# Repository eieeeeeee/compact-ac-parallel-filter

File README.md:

# Compact AC Parallel Filter

Open-hardware research platform for compact plug-in AC-noise filtering and adaptive parallel-shunt control.

> [!WARNING]
> **PRE-PROTOTYPE / EXPERIMENTAL / NOT MAINS-VALIDATED**
>
> No RC18 physical prototype has yet been manufactured or validated on hazardous mains power. The RC18 active-control work in this repository is currently a **low-voltage architecture and simulation study**. A safe mains coupling/isolation implementation is **not defined by the RC18 simulation model**. Do not interpret simulation, KiCad DRC/ERC, or CI results as safety approval, PSE compliance, EMC certification, or production readiness.

## What makes this repository different

The project publishes not only schematics and PCB files, but also the assumptions, comparison baseline, dense frequency sweeps, corner cases, controller coefficients, numerical implementation checks, and machine-executable pass/fail gates used to make design decisions.

A design change should be able to answer a simple question automatically:

> Does this change still meet the frozen electrical gates, or not?

## Current research branches

| Track | Purpose | State |
|---|---|---|
| Passive plug-in network | Compact X2/MOV/fuse parallel network | Pre-prototype |
| Rev.D / RC17 | Frozen comparison baseline for adaptive active-shunt studies | Simulation reference |
| **RC18-B2.1** | Lower-cost EPC23104 + 3 MHz + asymmetric 3-stage reconstruction + digital biquad | **Simulation gate PASS candidate** |

## RC18-B2.1 frozen candidate

The active-control candidate currently under validation is intentionally kept separate from the mains-safety question.

### Power/control architecture

- EPC23104 integrated GaN power stage
- 3.0 MHz PWM
- 2.0 MHz digital control update
- 0.82 µH / 150 nF first reconstruction section
- 0.47 µH / 100 nF second section
- 0.68 µH / 82 nF third section
- final float32/Q31 biquad validation at total modeled latency 2.041 µs
- bounded timing jitter: ±25 ns

### Frozen digital biquad

```text
H(z) = (b0 + b1 z^-1 + b2 z^-2) / (1 + a1 z^-1 + a2 z^-2)

b0 =  1.96005549
b1 = -2.81840199
b2 =  0.92560172
a1 = -1.02969083
a2 =  0.09694605
Fs = 2.000 MHz
```

### Electrical simulation gates

The CI gate evaluates:

- 241 logarithmic points from 5–30 kHz
- 241 logarithmic points from 30–100 kHz for watchdog testing
- source |Z| = 0.2 / 0.5 / 1 / 2 / 5 / 10 / 20 Ω
- source phase = −60° to +60° in 15° steps
- B2.1 nominal, low-L/C and high-L/C corners
- float32 sequential arithmetic
- Q31 CMSIS-style DF1 arithmetic model
- ±25 ns bounded timing jitter
- active current ceiling = 120 mArms
- command ceiling = 3.39411255 Vrms
- watchdog worsening ≤ +0.5 dB
- strict same-model RC17 equivalence requirement

The current self-contained validation script passes both float32 and Q31 gates. The exact result is regenerated in CI rather than accepted from a hand-edited table.

## Reproduce the RC18 gate locally

```bash
python -m pip install -r simulations/rc18-b2.1/requirements.txt
python simulations/rc18-b2.1/validate_rc18.py
```

Generated results are written under `validation/rc18-b2.1/generated/` by default.

See:

- [`docs/RC18-B2.1-VALIDATION-SPEC.md`](docs/RC18-B2.1-VALIDATION-SPEC.md)
- [`docs/REPRODUCIBILITY.md`](docs/REPRODUCIBILITY.md)
- [`simulations/rc18-b2.1/README.md`](simulations/rc18-b2.1/README.md)
- [`firmware/rc18-b2.1/biquad_coeffs.h`](firmware/rc18-b2.1/biquad_coeffs.h)
- [`validation/rc18-b2.1/README.md`](validation/rc18-b2.1/README.md)

## Repository structure

```text
.
├─ .github/workflows/          # KiCad and electrical validation CI
├─ hardware/                   # KiCad design work
├─ firmware/                   # Controller implementation material
├─ simulations/                # Reproducible models and gate scripts
├─ validation/                 # Frozen reference and generated results
├─ measurements/               # Physical measurements when prototypes exist
├─ bom/                        # BOM and sourcing work
├─ docs/                       # Design decisions, test plans, validation specs
├─ SAFETY.md
├─ CONTRIBUTING.md
├─ CITATION.cff
└─ LICENSE
```

## Evidence policy

Simulation results are predictions from disclosed models, not measurements. Null results, failed revisions, regressions, and negative measurements are part of the engineering record and should not be hidden.

Claims about real-world noise reduction will require controlled measurements using the same noise source, wiring, instrument settings, and comparison procedure. A future validated release should include raw data sufficient for independent re-analysis.

## Development path

`pre-prototype → low-voltage bench validation → isolated/safe interface design → controlled prototype test → independent reproduction → validated release`

A `v1.0` tag is reserved for a release whose documentation matches physically tested hardware.

## Safety and regulatory note

Open-source publication does not imply Japanese PSE compliance, IEC/UL compliance, EMC certification, safety approval, or fitness for connection to the public mains network. KiCad ERC/DRC only checks defined CAD rules; it cannot prove electrical safety or regulatory conformity.

Read [`SAFETY.md`](SAFETY.md) before working with any mains-related hardware in this repository.

## License

Hardware source material is published under **CERN-OHL-W-2.0** as described in [`LICENSE`](LICENSE).

---

## 日本語概要

このリポジトリは、コンセント直挿し型の並列ノイズ対策回路と、適応型アクティブ・シャント制御を研究するオープンハードウェア・プロジェクトです。

RC18では「回路図を公開する」だけではなく、比較基準、241点の周波数掃引、部品ばらつき、0.2～20 Ωのライン条件、±60°位相、watchdog、float32/Q31量子化、演算誤差、タイミングジッタまで公開し、GitHub Actionsで自動的にPASS/FAILを判定できる形を目指しています。

RC18-B2.1は現時点で**低電圧アーキテクチャのシミュレーション候補**です。商用電源へ安全に接続するための結合・絶縁方式は、このシミュレーションだけでは定義されていません。実機・商用電源試験・安全規格確認が終わるまで、完成品や安全確認済み製品として扱いません。

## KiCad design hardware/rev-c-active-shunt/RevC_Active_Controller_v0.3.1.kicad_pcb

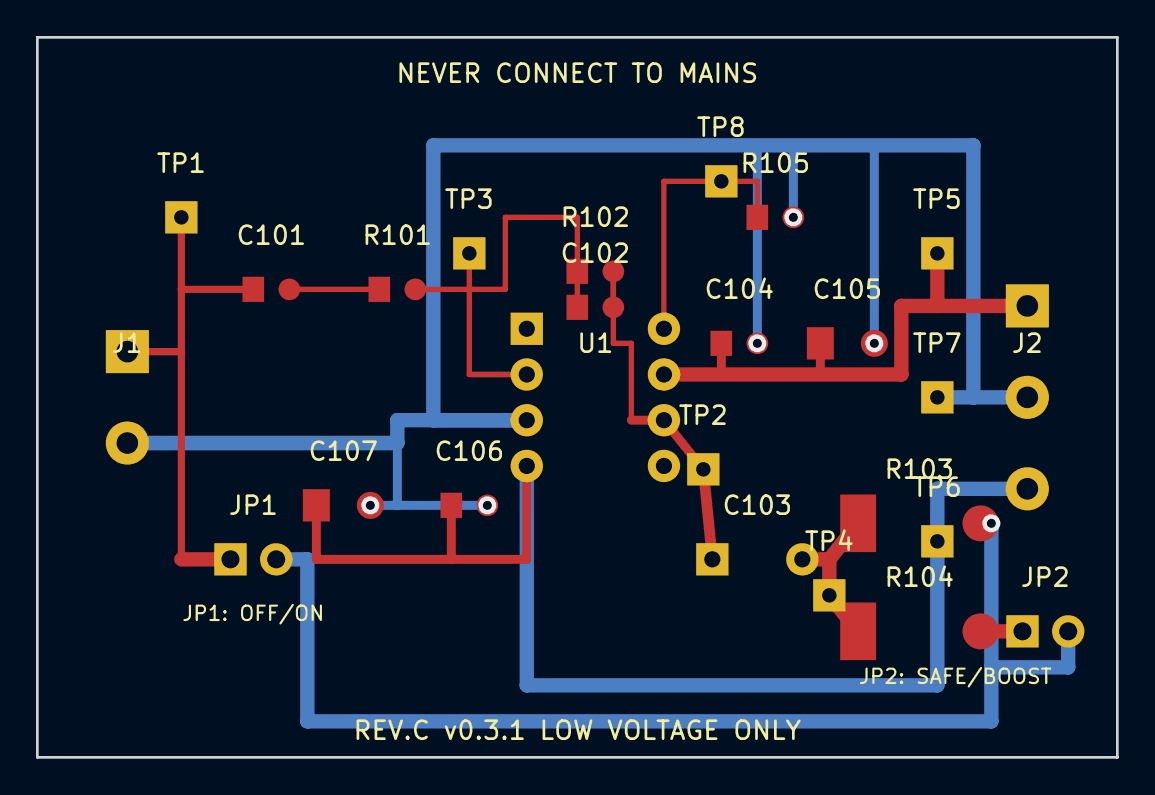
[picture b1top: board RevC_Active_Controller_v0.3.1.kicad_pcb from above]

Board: 2 copper layers, 60.0 x 40.0 mm, 25 parts (0 on the bottom side), 11 nets.

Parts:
C101: 15nF C0G; C_0805_2012Metric
C102: 330p C0G; C_0805_2012Metric
C103: 1uF FILM >=63V; C_FILM_P5
C104, C106: 100n; C_0805_2012Metric
C105, C107: 10u 25V; C_1206_3216Metric
J1: TEST_A / GND; Terminal_2P_5.08
J2: +12/GND/-12; Terminal_3P_5.08
JP1: ACTIVE ON; PinHeader_1x02_P2.54mm_Vertical
JP2: BOOST; PinHeader_1x02_P2.54mm_Vertical
R101: 2.00k 1%; R_0805_2012Metric
R102: 10.0k 1%; R_0805_2012Metric
R103: 47R 1W SAFE; R_2512_6332Metric
R104: 47R 1W BOOST; R_2512_6332Metric
R105: 47k FLAG; R_0805_2012Metric
TP1: TP1; TestPoint_THTPad_D1.5mm_Drill0.8mm
TP2: TP2; TestPoint_THTPad_D1.5mm_Drill0.8mm
TP3: TP3; TestPoint_THTPad_D1.5mm_Drill0.8mm
TP4: TP4; TestPoint_THTPad_D1.5mm_Drill0.8mm
TP5: TP5; TestPoint_THTPad_D1.5mm_Drill0.8mm
TP6: TP6; TestPoint_THTPad_D1.5mm_Drill0.8mm
TP7: TP7; TestPoint_THTPad_D1.5mm_Drill0.8mm
TP8: TP8; TestPoint_THTPad_D1.5mm_Drill0.8mm
U1: OPA551PA; DIP-8_W7.62mm

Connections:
/+12V: C104.1, C105.1, J2.1, TP5.1, U1.7
/-12V: C106.1, C107.1, J2.3, TP6.1, U1.4
/ACTIVE_SW: JP1.2, JP2.2, R103.2
/BOOST_SW: JP2.1, R104.2
/FLAG: R105.1, TP8.1, U1.8
/GND: C104.2, C105.2, C106.2, C107.2, J1.2, J2.2, R105.2, TP7.1, U1.3
/INJ_NODE: C103.2, R103.1, R104.1, TP4.1
/NINV: C102.1, R101.2, R102.1, TP3.1, U1.2
/OUT: C102.2, C103.1, R102.2, TP2.1, U1.6
/SENSE_CAP: C101.2, R101.1
/TEST_A: C101.1, J1.1, JP1.1, TP1.1

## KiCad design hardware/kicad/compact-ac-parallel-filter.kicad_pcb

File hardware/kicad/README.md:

# KiCad hardware

This directory contains two editable PCB studies. They are kept as separate revisions because their board size and implementation choices differ.

## Revision index

| Revision | KiCad | Board | Purpose | Status |
|---|---:|---:|---|---|
| Rev.A | 9 | 32 × 28 mm | compact mechanical study | pre-prototype |
| [review-v0.5](review-v0.5/README.md) | 10 | 50 × 35 mm | spacing and optional DNP branch study | official DRC: 0 violations |

Neither revision has been manufactured or tested on mains.

## Rev.A files in this directory

- `compact-ac-parallel-filter.kicad_pro` — project
- `compact-ac-parallel-filter.kicad_sch` — schematic
- `compact-ac-parallel-filter.kicad_pcb` — exact 32 × 28 mm PCB outline
- `ACP.kicad_sym` — local symbols
- `ACP.pretty/` — project-local footprints
- `PLACEMENT.csv` — placement coordinates

## Status

**PRE-PROTOTYPE / NOT YET TESTED ON MAINS.**

These files are for design review before fabrication. No physical-fit, mains, thermal, surge, EMC, PSE, or third-party safety validation has been completed.

## Rev.A mechanical basis

- PCB: **32.0 × 28.0 mm**
- nominal PCB thickness: **1.6 mm**
- C1: 22.5 mm lead pitch, 26.5 × 10 mm top-view body envelope
- MOV1: 7.5 mm nominal lead spacing; the footprint reserves a **17 mm maximum body envelope**
- F1: 5.08 mm pitch, 8.5 mm diameter envelope
- large THT parts are on the front; low-power resistor/LED/diode parts are on the back

At 32 × 28 mm the large-part courtyards are deliberately packed to the mechanical limit. If final creepage, clearance, enclosure or tolerance review fails, increase the PCB size rather than reducing safety margin.

## J1 limitation

`J1` is **not a Japanese/Type-A plug-blade footprint**. It is a provisional electrical interface to a separately mechanically retained plug assembly. Plug insertion/removal force must not be carried only by the PCB pads.

## Before ordering

1. Choose one reviewed hardware revision; do not mix files from different revisions.
2. Apply the final mains creepage/clearance rules for the actual regulatory environment.
3. Verify enclosure and component maximum dimensions against manufacturer drawings.
4. Verify every resistor's working/pulse voltage, power and flame behavior.
5. Verify the final LED and diode part numbers.
6. Replace J1 with the final plug/enclosure mechanical interface.
7. Review fuse/MOV coordination and abnormal-condition behavior.
8. Run ERC/DRC again with the exact ordered components and manufacturing rules.

## Rev.A topology

```text
AC L -- F1 --+-- C1 1uF X2 --+-- N
             |                |
             +-- MOV1 --------+
             |                |
             +-- R1 -- R2 ----+
             |                |
             +-- R4 -- R5 -- LED1 --+
                              |      |
                              +--D1--+  reverse clamp
                                     |
                                     N
```

C2 and optional RC damping are intentionally not implemented on the 32 × 28 mm Rev.A PCB. The 50 × 35 mm review-v0.5 board provides DNP footprints for measurement-driven comparison.

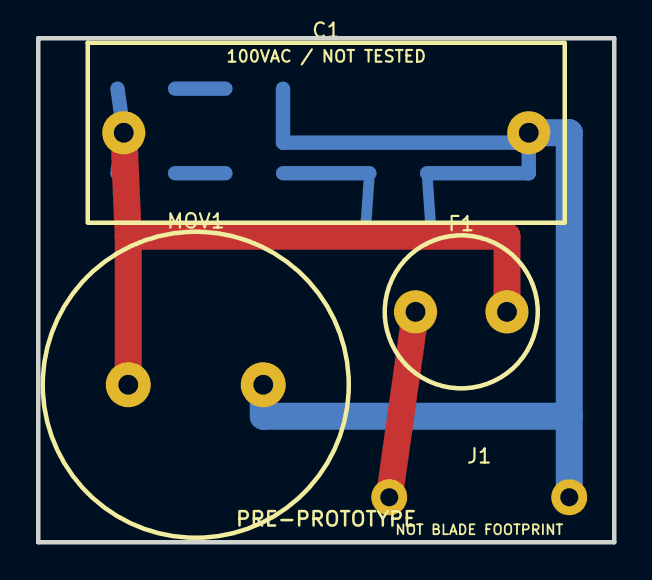
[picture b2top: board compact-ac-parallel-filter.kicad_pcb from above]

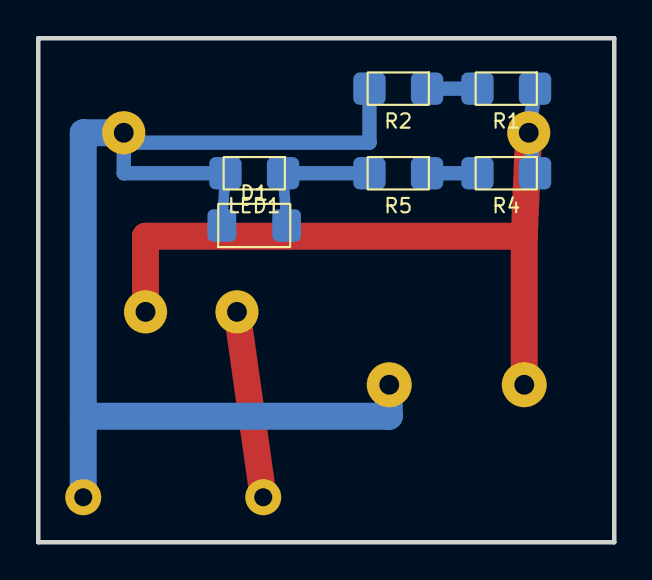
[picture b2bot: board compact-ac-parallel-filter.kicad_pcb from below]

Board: 2 copper layers, 32.0 x 28.0 mm, 10 parts (6 on the bottom side), 6 nets.

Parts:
C1: R533N410050P0K; R53_1uF_22.5mm
D1: 1N4148W reverse clamp; D_SOD123
F1: 37402500000; TR5_374_5.08mm
J1: PROVISIONAL PLUG INTERFACE; AC_Input_Pads_10mm
LED1: Blue LED; LED_1206
MOV1: TMOV14RP140E; TMOV14_7.5mm
R1, R2: 220k; R_1206
R4, R5: 47k; R_1206

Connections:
AC_L: F1.1, J1.1 (L)
DISCH_MID: R1.2, R2.1
LED_A: D1.2 (K), LED1.1 (A), R5.2
LED_RMID: R4.2, R5.1
L_FUSED: C1.1, F1.2, MOV1.1, R1.1, R4.1
N: C1.2, D1.1 (A), J1.2 (N), LED1.2 (K), MOV1.2, R2.2

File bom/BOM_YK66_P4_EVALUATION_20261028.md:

# YK66 Rev45U P4 — 評価試作用部品表
作成日: 2026-10-28
対象: 50×32mm、2層、板厚1.6mm。PCB blob 9545336db3f86ee7a858b75458c8d7f374d018e8。
製造データrun: 40661228439。これは評価試作の組立指定であり、製品安全・量産適合の承認ではない。

旧 bom/BOM.md は32×28mm Rev.A用。今回の基板へ使用しない。
本表は基板から13実装部品を抽出し、LEDとダイオードに評価用の発注型番を指定した。基板ファイルのTBD表記・銅箔・形状は変更していない。

| Ref | 数量/基板 | メーカー | 発注型番 | 値・形状 | 確認状態 |
|---|---:|---|---|---|---|
| C1 | 1 | TDK/EPCOS | B32923M3105M003 | 1µF ±20%、305Vrms、X2、22.5mmピッチ | 既存指定。公式製品情報照合済み |
| F1 | 1 | Littelfuse | 0216002.MXEP | 216シリーズ、アキシャル | 既存指定を維持。保証された時間電流特性・実装後保護協調は別途 |
| MOV1 | 1 | Littelfuse | TMOV14RP175E | 熱保護付きMOV | 既存指定を維持。採用理由・保護協調の最終確認は別途 |
| TCO1 | 1 | Sensience/MICROTEMP | G4A01098C | G4温度ヒューズ | 既存指定を維持。納入品の承認・リード加工・C1への熱結合を確認 |
| J1 | 1 | Phoenix Contact | 1711725 | MKDS 3/2-5,08、2極 | 1.30mm穴への公差込み挿入保証は未確定 |
| RL1、RL2 | 2 | YAGEO | RC2512FK-07150KL | 150kΩ ±1%、2512、1W/70℃ | 公式個別仕様書照合済み。実装温度・過渡耐量は別評価 |
| RB1〜RB4 | 4 | YAGEO | RC2512FK-07220KL | 220kΩ ±1%、2512、1W/70℃ | 公式個別仕様書照合済み。難燃・故障時安全の保証を意味しない |
| D1 | 1 | Vishay | 1N4148W-E3-08 | SOD-123 | 評価試作用のメーカー・発注型番を指定 |
| LED1 | 1 | Kingbright | APT3216QWF/G | 白色、1206、3.2×1.6×0.75mm | 評価試作用に選定。微小電流での明るさは未保証 |
| PCB | 1 | 基板製造業者 | 検証済みrunのGerber/Excellon | 50×32mm、2層、1.6mm | 発注仕様書を参照 |

## 接続・組立上の必須対応
基板は独自パッド番号を使う。部品メーカーの端子番号をそのまま基板番号へ対応させない。

| 部品 | A（アノード） | K（カソード） |
|---|---|---|
| LED1 | 基板pad1、/LED_A、(3.7,20.2)mm | 基板pad2、/N、(7.7,20.2)mm |
| D1 | 基板pad1、/N、(7.0,23.0)mm | 基板pad2、/LED_A、(3.0,23.0)mm |

Kingbright図面では端子1=K、端子2=A。本基板のpad1=A、pad2=Kとは逆なので、極性マークを基板pad2(/N)側へ対応させる。Vishay D1のカソード帯は/LED_Aへ対応させる。
座標は基板ファイルの絶対座標であり、裏面を目視した左右方向の指示ではない。

## LEDの形状と明るさ
- メーカー推奨ランドは各1.75×1.5mm、内側間隔2.0mm。現行LEDランドは各2.0×1.8mm、内側間隔2.0mmで、公称形状は推奨ランドを包含する。メーカー推奨と同一ではなく、はんだ量・位置ずれ・実装結果を現物確認する。
- 光度仕様は20mA時。RL1+RL2=300kΩの現行回路はそれより小さい電流となるため、掲載光度をそのまま適用しない。
- 100Vrms、正弦波、抵抗300kΩ、LED順方向電圧を仮に3.3Vとした理想計算: LED電流ピーク約0.460mA、全周期平均約0.145mA。これはシミュレーション・測定結果ではなく、微小電流での明るさも保証しない。
- まず絶縁された低電圧定電流源で0.1〜0.5mAの範囲を評価し、予定の窓・ライトパイプを介した視認性を確認する。今回、抵抗値や基板配線は変更しない。

## 放電抵抗の構成
(RB1+RB2)と(RB3+RB4)の2枝並列。合成220kΩ、C1=1µFの理想時定数0.22秒。
旧Rev.A部品表の440kΩ・0.44秒は今回の基板に適用しない。抜去後の実電圧は別途測定する。

## 一次資料
- LED: https://www.kingbrightusa.com/images/catalog/spec/APT3216QWF-G.pdf （V.6B）
- D1: https://www.vishay.com/docs/86356/1n4148w.pdf （Rev.1.0）
- RL: https://yageogroup.com/component-documentation/download/spec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
- RB: https://yageogroup.com/component-documentation/download/spec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
- C1: https://product.tdk.com/en/search/capacitor/film/emi-suppres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
- J1: https://www.phoenixcontact.com/en-in/products/printed-circui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
- TCO: https://www.sensience.com/wp-content/uploads/2023/10/G4-Micr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

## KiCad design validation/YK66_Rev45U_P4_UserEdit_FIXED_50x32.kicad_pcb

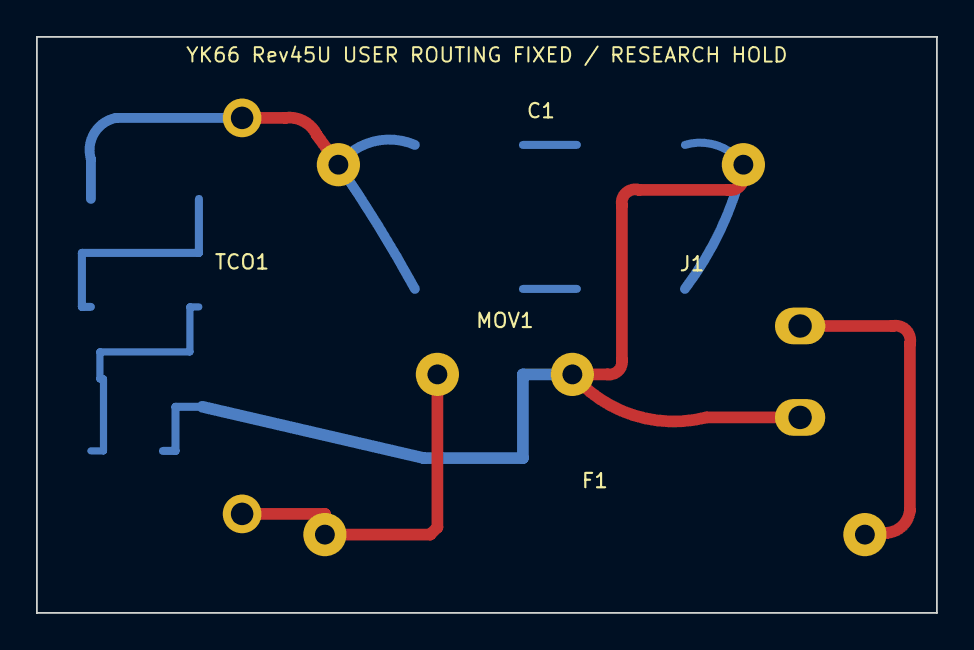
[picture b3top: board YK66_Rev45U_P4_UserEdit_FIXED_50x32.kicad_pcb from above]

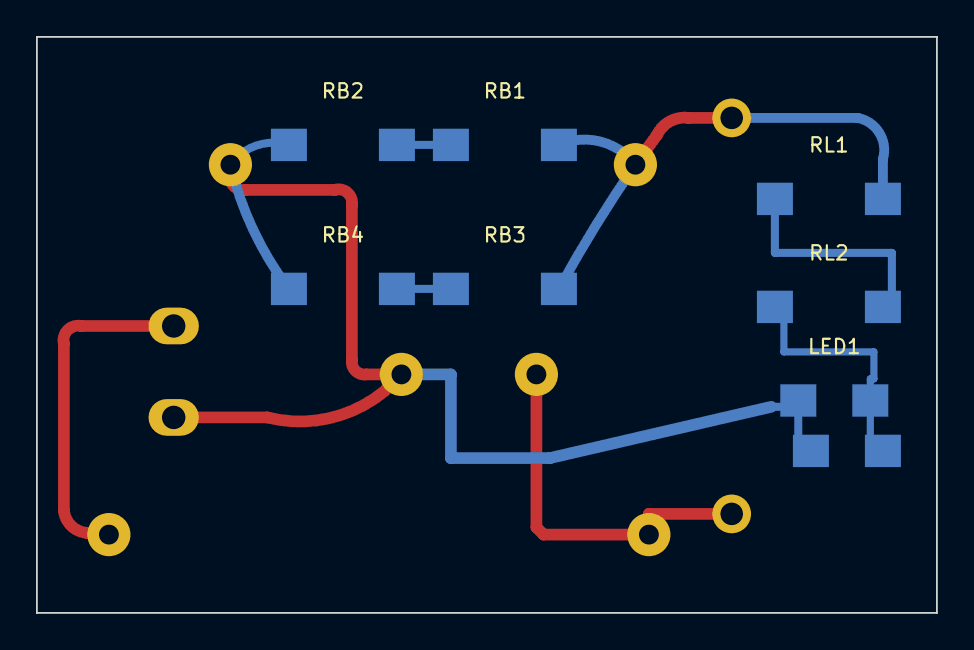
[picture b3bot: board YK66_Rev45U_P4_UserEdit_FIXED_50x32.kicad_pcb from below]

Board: 2 copper layers, 50.0 x 32.0 mm, 13 parts (8 on the bottom side), 8 nets.

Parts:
C1: B32923M3105M003; C_X2_22p5
D1: 1N4148W; D_SOD123_Bottom
F1: 0216002.MXEP; F_216_Axial_30p0
J1: PHOENIX_1711725_2P_5p08; Phoenix_1711725_MKDS3_2_5p08_PRELIM
LED1: WHITE_1206_HI_EFF_TBD; LED_1206_Bottom
MOV1: TMOV14RP175E; MOV_TMOV14_7p5
RB1, RB2, RB3, RB4: 220k_RC2512FK-07220KL; R_2512_Bottom
RL1, RL2: RC2512FK-07150KL; R_2512_Bottom
TCO1: G4A01098C; TCO_Axial_22p0

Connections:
/AC_A: F1.2, J1.1
/BLEED_M1: RB1.2, RB2.1
/BLEED_M2: RB3.2, RB4.1
/C_HOT: C1.1, RB1.1, RB3.1, RL1.1, TCO1.2
/FUSED: F1.1, MOV1.1, TCO1.1
/LED_A: D1.2, LED1.1, RL2.2
/LED_R1MID: RL1.2, RL2.1
/N: C1.2, D1.1, J1.2, LED1.2, MOV1.2, RB2.2, RB4.2
